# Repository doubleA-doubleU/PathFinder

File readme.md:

PathFinder Line-Following Differential Drive Robot

Android phone (Samsung Galaxy S5)
Microchip PIC32MX250F128B microcontroller
Custom PCB with mounting holes for:
	28 Pin DIP socket
	Mini USB connector
	Slideswitch
	MCP1702 voltage regulator (TO92)
	3mm red LED with 330 Ohm resistor
	Reset button with 10 kOhm resistor
	3mm green LED with 330 Ohm resistor
	User button with 10 kOhm resistor
	8 MHz crystal resonator
	4x 0.1 uF capacitors
	2x 10 uF polarized capacitors
	5-pin breakout for PICkit3 programmer
	2x 8-pin breakouts for remaining I/O pins and power/ground connections
2x 12V N20 DC motor w/ 298:1 gearhead (running on 5V from phone)
2x brass hex head (12.5mm) motor coupler with set screws
Towerpro SG90 micro servo
DRV8835 H-bridge https://www.pololu.com/product/2135
HTC Vive Position Sensor (TS3633-CM1) https://www.triadsemi.com/product/ts3633-cm1/
3D printed:
	Chassis
	2x wheels
	2x motor mounts
	Caster socket
5/8 inch ball bearing
4x M3x10mm bolts w/ hex nuts and washers
2x M4x10mm bolts
1x M3x20mm bolt w/ hex nut and washer
2x 2 inch o-rings
Elastic band to hold phone in place
USB OTG cable (micro to mini)

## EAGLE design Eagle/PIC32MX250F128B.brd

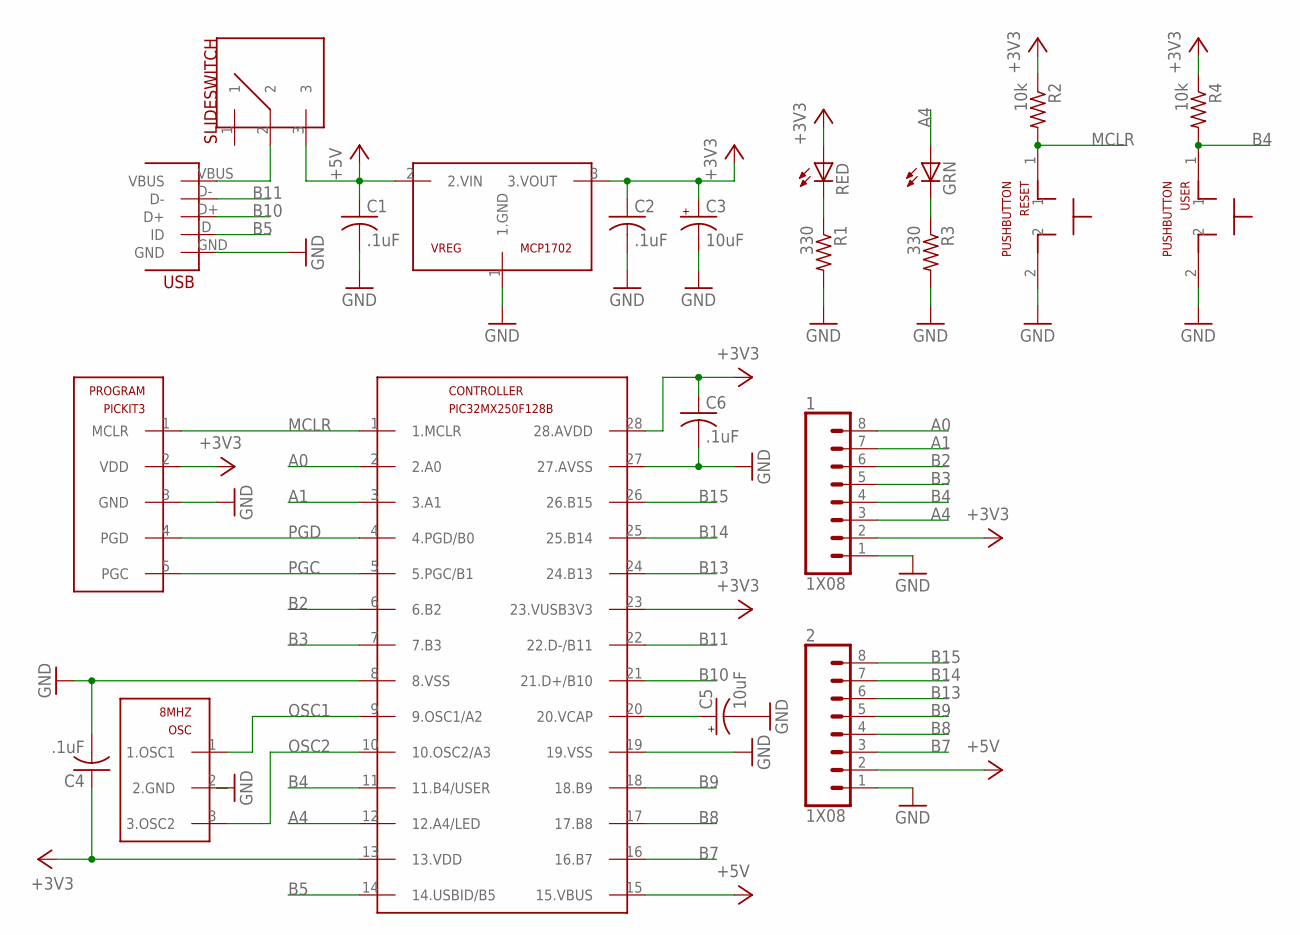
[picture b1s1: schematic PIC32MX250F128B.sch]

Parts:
1, 2: 1X08; CONN_08
8MHZ: OSC
C1, C2, C4, C6: .1uF; C025-025X050
C3, C5: 10uF; B45181B
CONTROLLER: PIC32MX250F128B; DIL28-3
GRN: LED3MM
PROGRAM: PICKIT3
R1, R3: 330; 0207/10
R2, R4: 10k; 0207/10
RED: LED3MM
RESET: PUSHBUTTON
SLIDESWITCH: SLIDESWITCH
USB: MINIUSB; USB-MB-H
USER: PUSHBUTTON
VREG: MCP1702; TO92

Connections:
+3V3: 1.2, C2.1, C3.+, C4.1, C6.1, CONTROLLER.13 (13.VDD), CONTROLLER.23 (23.VUSB3V3), CONTROLLER.28 (28.AVDD), PROGRAM.2 (VDD), R2.1, R4.1, RED.A, VREG.3 (3.VOUT)
+5V: 2.2, C1.1, CONTROLLER.15 (15.VBUS), SLIDESWITCH.3, VREG.2 (2.VIN)
A0: 1.8, CONTROLLER.2 (2.A0)
A1: 1.7, CONTROLLER.3 (3.A1)
A4: 1.3, CONTROLLER.12 (12.A4/LED), GRN.A
B2: 1.6, CONTROLLER.6 (6.B2)
B3: 1.5, CONTROLLER.7 (7.B3)
B4: 1.4, CONTROLLER.11 (11.B4/USER), R4.2, USER.1
B5: CONTROLLER.14 (14.USBID/B5), USB.ID
B7: 2.3, CONTROLLER.16 (16.B7)
B8: 2.4, CONTROLLER.17 (17.B8)
B9: 2.5, CONTROLLER.18 (18.B9)
B10: CONTROLLER.21 (21.D+/B10), USB.D+
B11: CONTROLLER.22 (22.D-/B11), USB.D-
B13: 2.6, CONTROLLER.24 (24.B13)
B14: 2.7, CONTROLLER.25 (25.B14)
B15: 2.8, CONTROLLER.26 (26.B15)
GND: 1.1, 2.1, 8MHZ.2 (2.GND), C1.2, C2.2, C3.-, C4.2, C5.-, C6.2, CONTROLLER.8 (8.VSS), CONTROLLER.19 (19.VSS), CONTROLLER.27 (27.AVSS), PROGRAM.3 (GND), R1.2, R3.2, RESET.2, USB.GND, USER.2, VREG.1 (1.GND)
MCLR: CONTROLLER.1 (1.MCLR), PROGRAM.1 (MCLR), R2.2, RESET.1
unnamed: R1.1, RED.K (C)
unnamed: GRN.K (C), R3.1
OSC1: 8MHZ.1 (1.OSC1), CONTROLLER.9 (9.OSC1/A2)
OSC2: 8MHZ.3 (3.OSC2), CONTROLLER.10 (10.OSC2/A3)
PGC: CONTROLLER.5 (5.PGC/B1), PROGRAM.5 (PGC)
PGD: CONTROLLER.4 (4.PGD/B0), PROGRAM.4 (PGD)
VBUS: SLIDESWITCH.2, USB.VBUS
VCAP: C5.+, CONTROLLER.20 (20.VCAP)

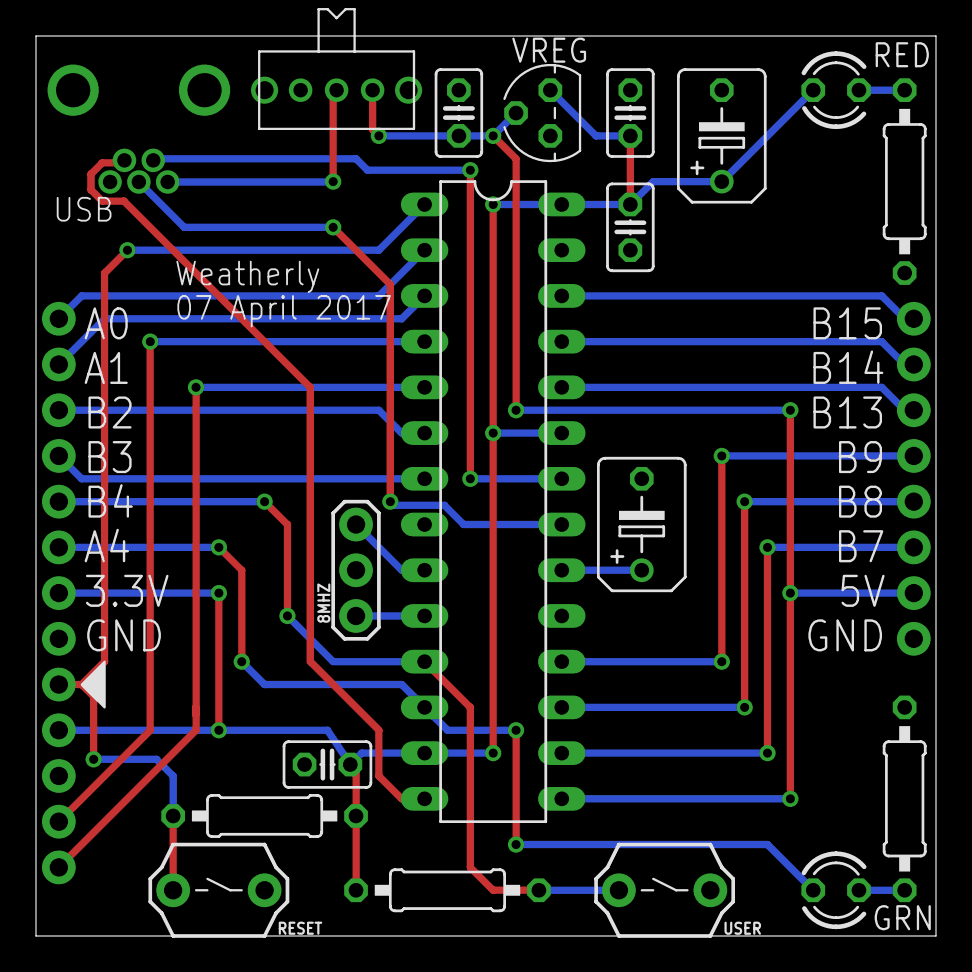
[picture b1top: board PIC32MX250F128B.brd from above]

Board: 2 copper layers, 50.0 x 50.0 mm, 22 parts (0 on the bottom side), 27 nets.

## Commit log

2017-06-13 :tada: Added .gitattributes & .gitignore files
2017-06-13 PathFinder
2017-10-26 Updated vive tracking and path color
